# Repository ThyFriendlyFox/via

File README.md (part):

# Via

[Website](https://via-kappa-five.vercel.app) · [Contract](WORKCENTER.md) · [Status](ee-agent-kit/STATUS.md) · [Roadmap](ee-agent-kit/ROADMAP.md)

Via is the EE Workcenter. A workcenter is a set of tools, skills and gates
that an agent steps into to do one kind of work well. This one does
electronics: it turns a KiCad 10 project into fabrication outputs that
passed every gate.

<a href="https://via-kappa-five.vercel.app">
  <picture>
    <source media="(prefers-color-scheme: dark)" srcset="site/media/hero-dark.png">
    
  </picture>
</a>

The fixture board `tests/boards/pass-first-design`: lines of its design
file, then the schematic and the routed board that `workcenter design`
writes from the file. The middle card shows the circuit's part of the
sheet.

2 runs of the gates, as the terminal printed them: that board, and a
fixture board with a clearance error on purpose.

```text
$ workcenter gates tests/boards/pass-first-design
PASS   erc        0 errors, 0 warnings  [0.41s]
PASS   drc        0 errors, 0 warnings (0 unconnected, 0 parity)  [0.75s]
PASS   sim        1 decks, 46 corner runs, 0 failures  [0.23s]
PASS   export     4/4 outputs, 22 gerber files  [1.6s]
GREEN: divider  report /home/user/via/tests/boards/pass-first-design/build/gates.json

$ workcenter gates tests/boards/fail-drc-clearance
PASS   erc        0 errors, 0 warnings  [0.27s]
FAIL   drc        1 errors, 1 warnings (0 unconnected, 0 parity)  [0.63s]
       - error: clearance: Clearance violation ( clearance 0.2000 mm; actual 0.0500 mm)
       - warning: track_dangling: Track has unconnected end
RED: rc_divider  report /home/user/via/tests/boards/fail-drc-clearance/build/gates.json
```

<table>
  <tr>
    <td width="50%"></td>
    <td width="50%"></td>
  </tr>
  <tr>
    <td>The same board, turned. <code>workcenter render</code> draws it with <code>--views spin</code>.</td>
    <td>Each layer that holds something. <code>workcenter render</code> draws 1 picture for each and this sheet.</td>
  </tr>
</table>

The 3D views show the part bodies of KiCad's own library. `install.sh`
installs none of them, and without them the same command draws the bare
board. [site/media/README.md](site/media/README.md) has each picture, how
to fetch the 3 bodies, and the whole command that draws it.

## An example: Herald, a fire alarm communicator

[`examples/fire-alarm-communicator/v0.1`](examples/fire-alarm-communicator/v0.1/README.md) sits
beside a fire alarm panel and reports to a monitoring station over LTE-M, with Wi-Fi as the second
path. 84.4 x 64 mm, 4 layers, every part on the front, red with a white legend and black terminals.
It answers the panel's own phone dialer as if it were the line: a current-limited loop feed, dial
tone and the handshake from a PWM pin, and the panel's DTMF digits decoded in firmware with a
Goertzel filter. 3 supervised inputs read a closed contact, a whole loop and a cut wire apart at
every corner, and a fail-safe relay tells the panel when Herald itself fails.

## An example: Rosetta, a universal controller

[`examples/universal-controller/v0.2`](examples/universal-controller/v0.2/README.md) is a game
controller made with the workcenter: a 5-position knob picks a PS4, a PS5, an Xbox, a Switch or
Bluetooth. Its board is laid out like an Xbox 360 controller's, 148 x 82 mm, 6 layers, routed
and GREEN: thumbsticks soldered on (the footprint written from ALPS's drawing), Hall-effect
triggers on the shoulder horns, an RP2040 that runs a second USB port in software to relay a
console's signature to a licensed donor, an ESP32 whose antenna hangs past the dip between the
horns, and a knob read as 1 number whose 5 positions 6 decks prove never meet.

## An example: Signet, a mouse worn as a ring

[`examples/ring-mouse`](examples/ring-mouse/README.md) is a mouse you wear on the index finger, made
with the workcenter as a series of prototypes, a version per pass of a loop. Six 4-layer boards, 12
mm along the finger, sit on the faces of a hexagonal prism round it, each soldered to the next by 8
plated edge pads. The ring turns with the hand and the cursor follows its gyroscope; the thumb slides
along a 3-channel strip to scroll and presses the side to click. A Bluetooth LE module, a charger,
a 3.3 V rail and a 20 mAh cell ride on the other tiles, and every tile is GREEN.

## An example: Hush, a speaker that cancels noise

<table>
  <tr>
    <td width="50%"></td>
    <td width="50%"></td>
  </tr>
</table>

[`examples/anc-speaker/v0.1`](examples/anc-speaker/v0.1/README.md) is a ring 62 mm across that
sits on the face of a 40 mm speaker. A microphone on its hub listens 4 mm in front of the cone, and
an analog feedback loop plays the inverse of what it hears: 7 decks hold 3 dB less noise at 50 Hz
and 12 dB from 200 to 300 Hz at every one of 986 corner runs, and take a 150 Hz hum 18.8 dB down
(13.4 dB at the worst corner). Music from a phone plays through the loop as its target. The back
draws the idea: the noise and its inverse, meeting as one line.

## An example: Wyvern, a Snapdragon development board

[`examples/snapdragon-dev-board`](examples/snapdragon-dev-board/README.md) is a development board
with a Snapdragon on it, laid out like a Teensy and kept as version folders. v0.2 is one flat board,
76.2 x 53.34 mm, 6 layers, 2 rows of 30 pins: a Qualcomm QCS6490 on Vantron's VOSM6490 is soldered
straight on by its 662 pads, a land pattern generated from SGET's OSM standard. An RP2350 beside it
drives the pins at 3.3 V, and Linux flashes it over USB. A buck-boost holds the module's 5.0 V from
any USB-C cable, and an HD3SS3220 switches its USB 3 lane to the side the plug is on; the lane and
the converter's 0.25 mm power pads are drawn by hand in the design file.

## An example: Basalt, a microATX Threadripper board

[`examples/threadripper-matx`](examples/threadripper-matx/README.md) is a workstation motherboard
for an AMD Threadripper on sTR5, on a microATX board (244 x 244 mm), which no maker has built. It is
a prototype series built in a loop logged in its [`LOOP.md`](examples/threadripper-matx/LOOP.md),
one version a feature, each GREEN: v0.1 the floor plan, a 4844-land socket and 14 phases with every
supply in a pour; v0.2 the 4 DDR5 channels, 576 traces drawn by rule with 0 DRC errors on the first
run; v0.3 the ports and headers a desktop board carries, routed by the project's own grid router.
10 layers, black and silver.

## A chip: acc8, an 8-bit processor

Via also takes a chip from RTL to a GDSII mask layout: the drawing a
foundry etches from. The project is Verilog, benches, timing constraints
and `chip.json`. 10 gates run in order on open engines and the open
SkyWater 130 nm process, and stop at the first that does not pass.

<table>
  <tr>
    <td width="50%"></td>
    <td width="50%"></td>
  </tr>
  <tr>
    <td>The layout of <code>tests/chips/pass-acc8</code>, every layer: 760 cells on a die of 152.38 um by 152.38 um. <code>workcenter chip render</code> draws it.</td>
    <td>The second metal layer alone. The command draws 1 picture for each routing layer.</td>
  </tr>
</table>

acc8 is an accumulator processor with 16 opcodes and 4 programs in its
ROM. 5 benches make 1098 checks on the RTL, 4 of them again on the
routed netlist. The run, as the terminal printed it:

```text
$ workcenter chip gates tests/chips/pass-acc8 --strict
PASS   lint       4 RTL files, top acc8, 0 failures  [0.19s]
PASS   sim        5 benches, 1098 checks, 18 of 18 changes of the RTL caught, 0 failures  [0.74s]
PASS   synth      760 cells, 132 flops, 8530.7 um2, the mapping removed 24 flops that nothing reads (--json names each), 0 failures  [1.84s]
PASS   layout     8379.29 um2 of cells, utilisation 0.493, 0 failures  [194.64s]
PASS   sta        15 corners, least setup slack 25.1717 ns at max_ss_n40C_1v60, least hold slack 0.2974 ns at min_ff_n40C_1v95, 0 failures  [4.56s]
PASS   glsim      4 benches on the final netlist, 1 on the RTL only, 0 failures  [0.51s]
PASS   drc        2 decks: magic 0, klayout-mr 0, 0 failures  [15.16s]
PASS   antenna    the routed database, 0 failures  [0.31s]
PASS   lvs        the layout against the netlist with its supply pins: 792 devices against 792, 0 failures  [2.82s]
PASS   export     22 files, 20 reports and manifest.json in chip/tapeout, 0 failures  [0.37s]
scope: open engines, sky130A 1.0.470-0-g6d4d117, decks: magic (community), klayout-mr (community), corners: max_ss_n40C_1v60, max_ss_100C_1v60, max_ff_n40C_1v95, max_ff_100C_1v95, max_tt_025C_1v80, min_ss_n40C_1v60, min_ss_100C_1v60, min_ff_n40C_1v95, min_ff_100C_1v95, min_tt_025C_1v80, nom_ss_n40C_1v60, nom_ss_100C_1v60, nom_ff_n40C_1v95, nom_ff_100C_1v95, nom_tt_025C_1v80; no foundry deck ran; no shuttle's limits were checked
GREEN: pass-acc8  report /home/user/via/tests/chips/pass-acc8/build/gates.json
```

| Gate | What it holds |
|---|---|
| LINT, SIM | The RTL reads the same to a simulator and to a synthesizer. Every bench passes, and every listed change of the RTL fails a bench: a bench that passes on a wrong design proves nothing. |
| SYNTH, LAYOUT | The RTL maps onto the library's cells, with a reset on every flop. The cells are placed and routed with no violation. |
| STA, GLSIM | Timing holds at every corner of temperature and supply the project names, with the routed wires. The benches pass again on the routed netlist. |
| DRC, ANTENNA, LVS | The layout breaks no rule of 2 decks, no wire collects too much charge, and the layout is the netlist, device by device. |
| EXPORT | The layout is handed out only when each of the 9 gates passed on the files as they are now. |

The line before the verdict is the scope of the run. GREEN says that the
open engines found no fault in these files. It does not say that a foundry
accepts the layout or that the silicon works: no foundry deck runs here.

The engines install on request: `sudo ./install.sh --chip`.
`workcenter chip init <dir> --top <module>` starts a project, and
`workcenter next <dir>` names each step from there.
[`.claude/skills/chip-design/SKILL.md`](.claude/skills/chip-design/SKILL.md)
has the procedure, and [`tests/chips/README.md`](tests/chips/README.md)
the 9 fixture chips.

## What it does

| Part | In short |
|---|---|
| **Engines** | KiCad 10 (`kicad-cli`), ngspice, FreeRouting. |
| **Gates** | ERC, DRC, SIM, EXPORT, in that order. A board is done when `workcenter gates <project>` prints GREEN. |
| **Design as code** | `workcenter design design.py --route` builds a schematic and a routed board from a Python file that names parts from the KiCad libraries. No GUI at any step. |
| **A schematic that simulates** | The design file says how each part simulates (`d.sim`, `d.no_sim`), and the schematic KiCad opens exports a netlist ngspice runs. A pin map KiCad would complete by position is refused first. |
| **Decks** | The SIM gate runs the decks under `sim/` and holds each measured value to its bound. A deck is a file of its own. Nothing holds a deck typed by hand to the schematic's parts yet: the roadmap names that gap. |
| **Corners** | The SIM gate runs every deck at each temperature the project names and with each part at each end of its tolerance. It runs every combination of those ends up to 64 runs, and a worst case for each bound above that. It also runs the Monte Carlo draws the project names. A bound holds at every corner or it does not hold. |
| **Frequency plan** | The SIM gate holds every switching frequency and its harmonics against every resonance a deck measured. |
| **The next step** | `workcenter next <project>` names the one step that is left, its command, and the fix for the first failure. A person or an agent of any size follows the same path. |
| **Skills** | Procedures for each kind of step, as Markdown files. |
| **Fixture boards** | The tests. Each passes everything or fails 1 named gate. |

## How it works

<picture>
  <source media="(prefers-color-scheme: dark)" srcset="site/media/diagram-dark.png">
  
</picture>

A design file becomes a KiCad project. The 4 gates judge the project in
order and stop at the first red. The last line of a run is the verdict:
GREEN, RED or SKIPPED. The fabrication outputs of a GREEN board are in
`build/fab/`.

## Quick start

```sh
sudo ./install.sh     # Ubuntu 24.04: KiCad 10, ngspice, Java 21, FreeRouting
workcenter doctor     # each engine's status; ok when nothing is absent
workcenter gates tests/boards/pass-first-design     # GREEN
workcenter gates tests/boards/fail-drc-clearance    # red at DRC, on purpose
workcenter next tests/boards/fail-drc-clearance     # the one next step: the fix
workcenter sim tests/boards/fail-sim-corner         # red at its corners, on purpose
workcenter sim tests/boards/fail-freq-overlap       # red on the frequency plan
```

Output goes to `<project>/build/`: `erc.json`, `drc.json`, `sim/`,
`fab/` (gerbers, drill, BOM, schematic PDF), `gates.json`.

A first board starts from a copy of the template's design file, in a
folder of its own outside this checkout:

```sh
mkdir ~/divider
cp templates/project/design.py ~/divider/
workcenter design ~/divider/design.py --route    # the KiCad project, routed
workcenter gates ~/divider --strict              # GREEN, and SIM has no deck to run yet
```

[`.claude/skills/board-design/SKILL.md`](.claude/skills/board-design/SKILL.md)
has the procedure from a spec to a GREEN board.

## Commands

`workcenter --help` describes each command, and
`workcenter <command> --help` lists its flags.
[`ee-agent-kit/docs/CONFIGURATION.md`](ee-agent-kit/docs/CONFIGURATION.md)
has every flag.

<details>
<summary>The 25 commands</summary>

| Command | What |
|---|---|
| `doctor` | Report each engine's status. |
| `next` | Name the one next step for a project. |
| `chip` | A chip project, from RTL to a GDSII layout: `chip init`, `chip gates`, 1 command for each of its 10 gates, and `chip render` for a picture of the layout. Tests hold all 10 gates. The acceptance design, an 8-bit processor of 760 cells on the sky130A process, is GREEN with `--strict` in under 4 minutes. |
| `design` | Build a design file into a KiCad project; `--route` routes it; `--check` compares. |
| `erc`, `drc`, `sim`, `export` | One gate, alone. |
| `gates` | The 4 gates in order; the last line is the verdict. |
| `verify` | Check a verification package against a fresh run; say whether the requirements are met. |
| `autoroute` | Write FreeRouting's session file for a hand-drawn board's DSN. The import into KiCad is by hand. |
| `inspect` | Read a routed board: `map`, `list`, `probe`, `net`, `islands`, `resistance`, `crossed`. |
| `placement` | Run a kistack placement check on a board. |
| `render`, `pictures` | Images of the schematic, the board, every layer; turning GIFs; assembly scenes. |
| `procure`, `costs` | Price a board's parts; price every board of every version. |
| `sources`, `fetch`, `curve` | Check each part's datasheet and model; fetch one; read a curve from a PDF. |
| `mutate` | Prove a firmware's host tests can fail. |
| `ci` | Replay a repository's GitHub workflow here. |
| `docs`, `version`, `diagram` | A version's contents page and datasheets; a new version folder; a block diagram. |

</details>

## Where it runs

**A Claude Code cloud environment.** The environment carries the
software; the project's repository carries the board. Create an environment
whose setup script is the 3 lines in
[`environment/setup.sh`](environment/setup.sh), with the network hosts from
[`environment/README.md`](environment/README.md). Open any project's
repository in it. Attach this repository as a second repository when its
skills should load.

**Another agent host.** `AGENTS.md` at the root is the entry for a host
that does not read `CLAUDE.md`; the 2 files are the same text. Every
procedure is a Markdown file under `.claude/skills/`, and every check is a
command. `workcenter next <project>` gives the step, and `make verify`
the repository's health.

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
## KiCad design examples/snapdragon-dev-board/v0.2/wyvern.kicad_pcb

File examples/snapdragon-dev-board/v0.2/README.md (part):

# Wyvern — board prototype v0.2

> The current version of the [Wyvern prototype series](../README.md), started as a copy of [`../v0.1/`](../v0.1/). The earlier version is the sibling folder [`../v0.1/`](../v0.1/).

A development board with a Snapdragon on it, on one flat board. The Qualcomm QCS6490 (8 Kryo 670
cores, 1 at 2.7 GHz, 3 at 2.4 GHz and 4 at 1.9 GHz; an Adreno 643; a Hexagon NPU of 12 TOPS; 8 GB of
LPDDR5 and 64 GB of eMMC) comes on Vantron's VOSM6490, a 45 x 45 mm OSM Size-L module that is soldered
straight onto the board by its 662 pads, like any other chip, and runs Linux or Android. Beside it, an
RP2350 drives 30 pins at 3.3 V the way a Teensy's microcontroller does; the Snapdragon resets it,
puts it in its bootloader and talks to it over USB, so Linux flashes it. The Snapdragon's own UART,
2 I2C buses, an SPI bus and 2 GPIOs are on the same rows at the module's end, at 1.8 V. One USB-C
cable powers the board and carries USB 3.

Wyvern lies flat on a bench, or stands in a breadboard on its 2 rows of pins, with one USB-C cable
at its left end. It is one board, 76.2 x 53.34 mm (3.0 x 2.1 inch) and 6 layers, with the module,
the USB-C, the power and the RP2350 on its top face and the microSD slot and the pins' names on its
bottom.

This folder is a whole KiCad 10 project made with the EE Workcenter: `design.py` is the board, and
the `.kicad_*` files beside it are what `workcenter design` writes from it.

| Item | State |
|---|---|
| Schematic | drawn with wires in blocks, the module's 662 pins in 13 banks named from the OSM standard and Vantron's datasheet; ERC <!-- erc -->0 errors, 0 warnings<!-- /erc -->; no parity warning |
| Board | 76.2 x 53.34 mm (3.0 x 2.1 in), **6 layers**, 1.6 mm, black mask, white legend, ENIG, made to Sierra Circuits' Web PCB limits; 2 rows of 30 pins on the 0.1 in grid, 2.0 in apart; the module, USB-C, the power, the RP2350 and the buttons on the top face, the microSD and the pins' names on the bottom |
| Gates | <!-- gates -->GREEN with 16 warnings: ERC 0 and 0; DRC 0 errors, 0 unconnected, 0 parity, 9 warnings (silkscreen at the edge, 4 vias with nothing past them); SIM 7 decks, 397 corner runs, 0 failures; EXPORT 4 of 4 (`docs/gates.md`)<!-- /gates --> |
| USB | the module's SuperSpeed lane through an HD3SS3220 to both sides of the USB-C receptacle, drawn by hand as 90 ohm pairs; CC by the HD3SS3220, which answers a charger with nothing else powered; the USB 2 pair to both rows |
| Power | 5 V from USB-C (or the 5V pin) to the module's 5.0 V by a TPS552892 buck-boost, 4.86 to 5.17 V at every corner; 3.3 V from that by an AP2112K; the module's own 1.8 V on 2 pins |
| Simulation | 7 decks, each at every corner of its parts' tolerances (`sim/`): the 5.0 V rail inside the module's window, where the converter starts, the USB input's resonance with a cable, the Snapdragon's I2C on the pins, the RP2350's reset and boot lines; a frequency plan holds the 3 clocks against the resonance |
| Parts and cost | an orderable part for every line (`../parts/catalog.csv`); the board's parts $34.18 for 1, $26.00 each for 10, with 4 lines not priced and each reason named; 7 lines out of stock at Digi-Key when read, most with a restock date; the module is sold by quote and not priced |
| Firmware | none yet |

## Images

| Top face | Bottom face (mirrored) |
|---|---|
|  |  |

| 3D, from above | 3D, from below |
|---|---|
|  |  |

| Turning, from above | Turning, from below |
|---|---|
|  |  |

| Every layer | The schematic |
|---|---|
|  |  |

From `workcenter pictures .` (its `pictures.json`), with KiCad's 3D bodies in `KICAD10_3DMODEL_DIR`
and the 5 bodies in `models/`. The module's body is a stand-in ("The Snapdragon module").

## What changed in v0.2: one flat board

The request, on 2026-11-12: "there's a LOT of open hinges here, power, data, alot of routing, it
looks like you slapped two board together too. Can it be one board for v0.2?"

| Finding | The owner's answer | What v0.2 does |
|---|---|---|
| v0.1 is 2 boards: the Open-Q 845 module stands 3 mm over the carrier on 3 sockets, 300 contacts to buy, align and mate | chose "Flat QCS6490 module" (2026-11-12): one flat board, about 53 x 76 mm, a 45 mm QCS6490 module soldered straight on, no sockets and no second board; 5 V in, 3.3 V pins along both long edges, USB-C at one end | the VOSM6490 sits on its 662-pad LGA, reflowed with every other part; the board is 76.2 x 53.34 mm ("The Snapdragon module") |
| Power: v0.1's module wanted 3.45 to 4.75 V from USB's 5 V through a buck whose input stood 0.13 ohm from oscillating with a long cable; this module wants 4.8 to 5.2 V, which a cable carrying 3 A does not deliver | part of the same answer: 5 V in | a TPS552892 buck-boost makes 5.0 V from any VBUS between 3.8 and 5.5 V (4.86 to 5.17 V at every corner), and a damper holds the cable's resonance at 0.51 ohm at worst against the converter's 1.33 ohm ("Power") |
| Data: v0.1 relied on the module's own Type-C controller and lane order, which its maker documents only in a carrier guide behind a registration | part of the same answer | an HD3SS3220 owns the plug: CC, orientation and the SuperSpeed lane, and it answers a charger before anything is powered; every module pad the board uses is named from Vantron's public pin tables ("USB-C") |
| Supply: Digi-Key lists the Open-Q 845 uSOM as obsolete | part of the same answer | the VOSM6490 carries the QCS6490 on SGET's open OSM standard, so its land pattern is public and other makers' OSM-L modules share it |

### Board

The module sets the board: 45 mm square between 2 rows of 30 pins 2.0 inch apart, its row A (its
USB-C lane) facing the USB-C end, its right edge 1.0 mm from the board's. The 31 mm left of it holds
everything else on the top face: the buttons down the left edge, the RP2350 block in the upper half
(v0.1's, turned a quarter turn), USB-C, its mux and the buck-boost in the lower half. The microSD
slot sits under the far end, its card standing out past the right edge. Every module pad the board
uses has a via in the middle of the 4 pads round it (`module_fanout`), so the router takes each
signal out from under the module on the inner layers. The router (FreeRouting) drew <!-- route -->1007 segments and 76 vias round
what `design.py` draws by hand: the buck-boost's power pads, the SuperSpeed lane through its mux,
the receptacle's B row, the RP2350's supplies and fan-out, the module's 184 vias and a spine that
holds the 5 V plane together under the module<!-- /route -->.

### Simulation

7 decks, run at every corner (`workcenter sim .`): the module's 5.0 V at 4.86 to 5.17 V against
its 4.8 to 5.2 V; where the buck-boost starts, 3.51 to 3.78 V of VBUS; the USB input's peak
impedance with a cable, 0.26 ohm at 37 kHz and 0.51 ohm at the worst corner against 1.33 ohm; the
Snapdragon's I2C on the pins, the RP2350's reset and boot lines. A frequency plan holds the
buck-boost, the RP2350's regulator and its crystal against the cable's resonance.

### Firmware

None yet ("Open items").

### Parts and cost

The module, the mux, the buck-boost and its inductor, 9 resistors and capacitors and the 1 x 30
headers are new; the RP2350 block's parts are v0.1's. `../parts/catalog.csv` names an orderable part
for each line, read on 2026-11-12; `workcenter costs ..` prices the board into `../parts/lists/`
("Bill of materials").

### Verification summary

No verification package yet ("Open items").

## What changed in v0.1: the first board

The request: a new microcontroller development board, something like a Teensy but with a Snapdragon
chip, compact, as the workcenter's example of what it can make. v0.1 carried a Snapdragon 845 on
Lantronix's Open-Q 845 uSOM, plugged into 3 DF40 sockets on a 61 x 30.5 mm stick, with an RP2350 on
the pins; its folder, [`../v0.1/`](../v0.1/), tells the rest.

## Architecture

```
USB-C (J1) ─VBUS─┬─ 5V pin
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
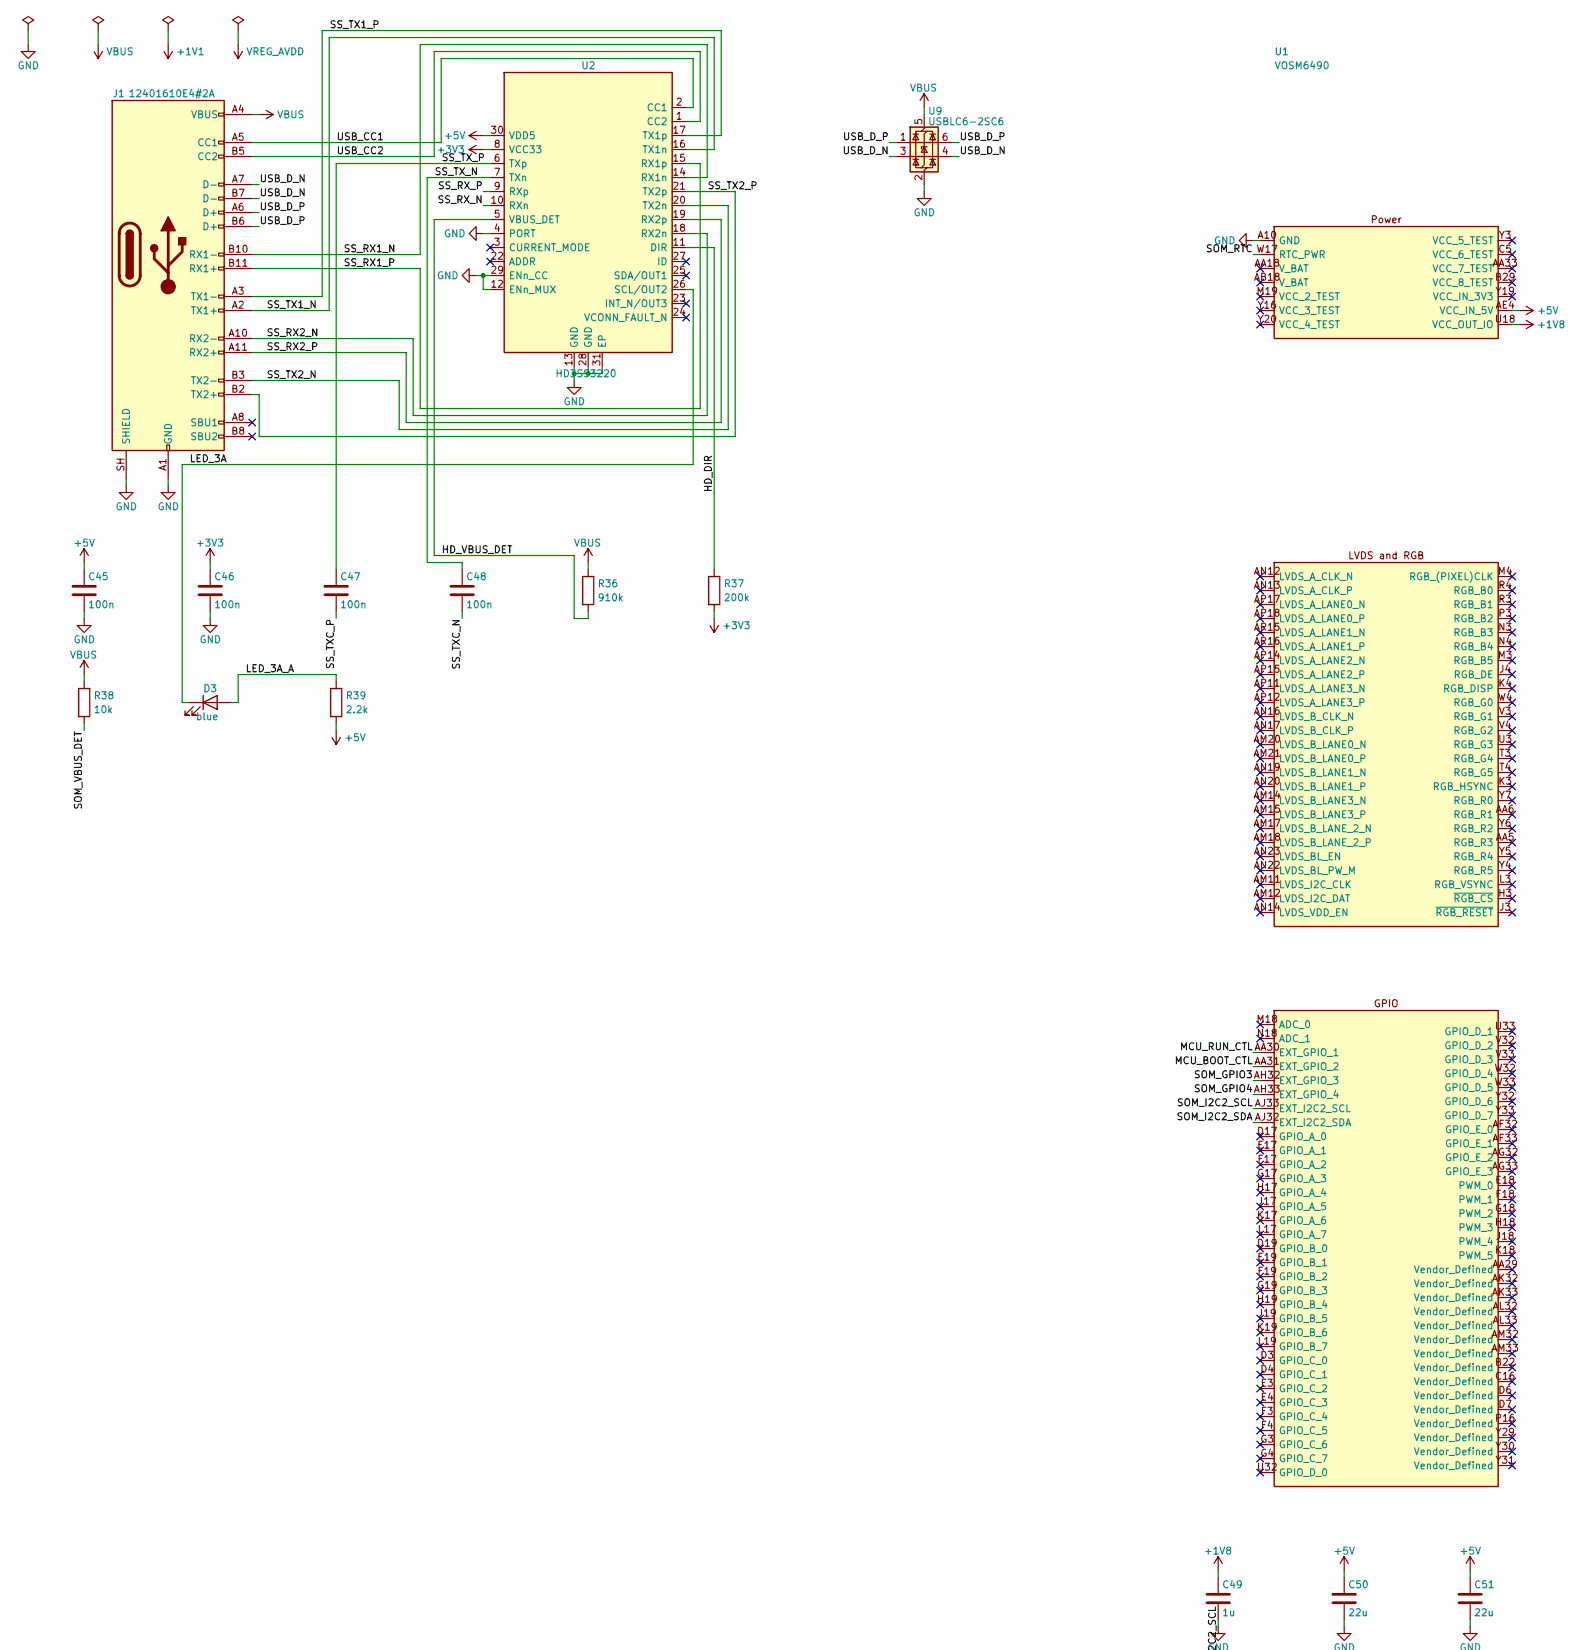
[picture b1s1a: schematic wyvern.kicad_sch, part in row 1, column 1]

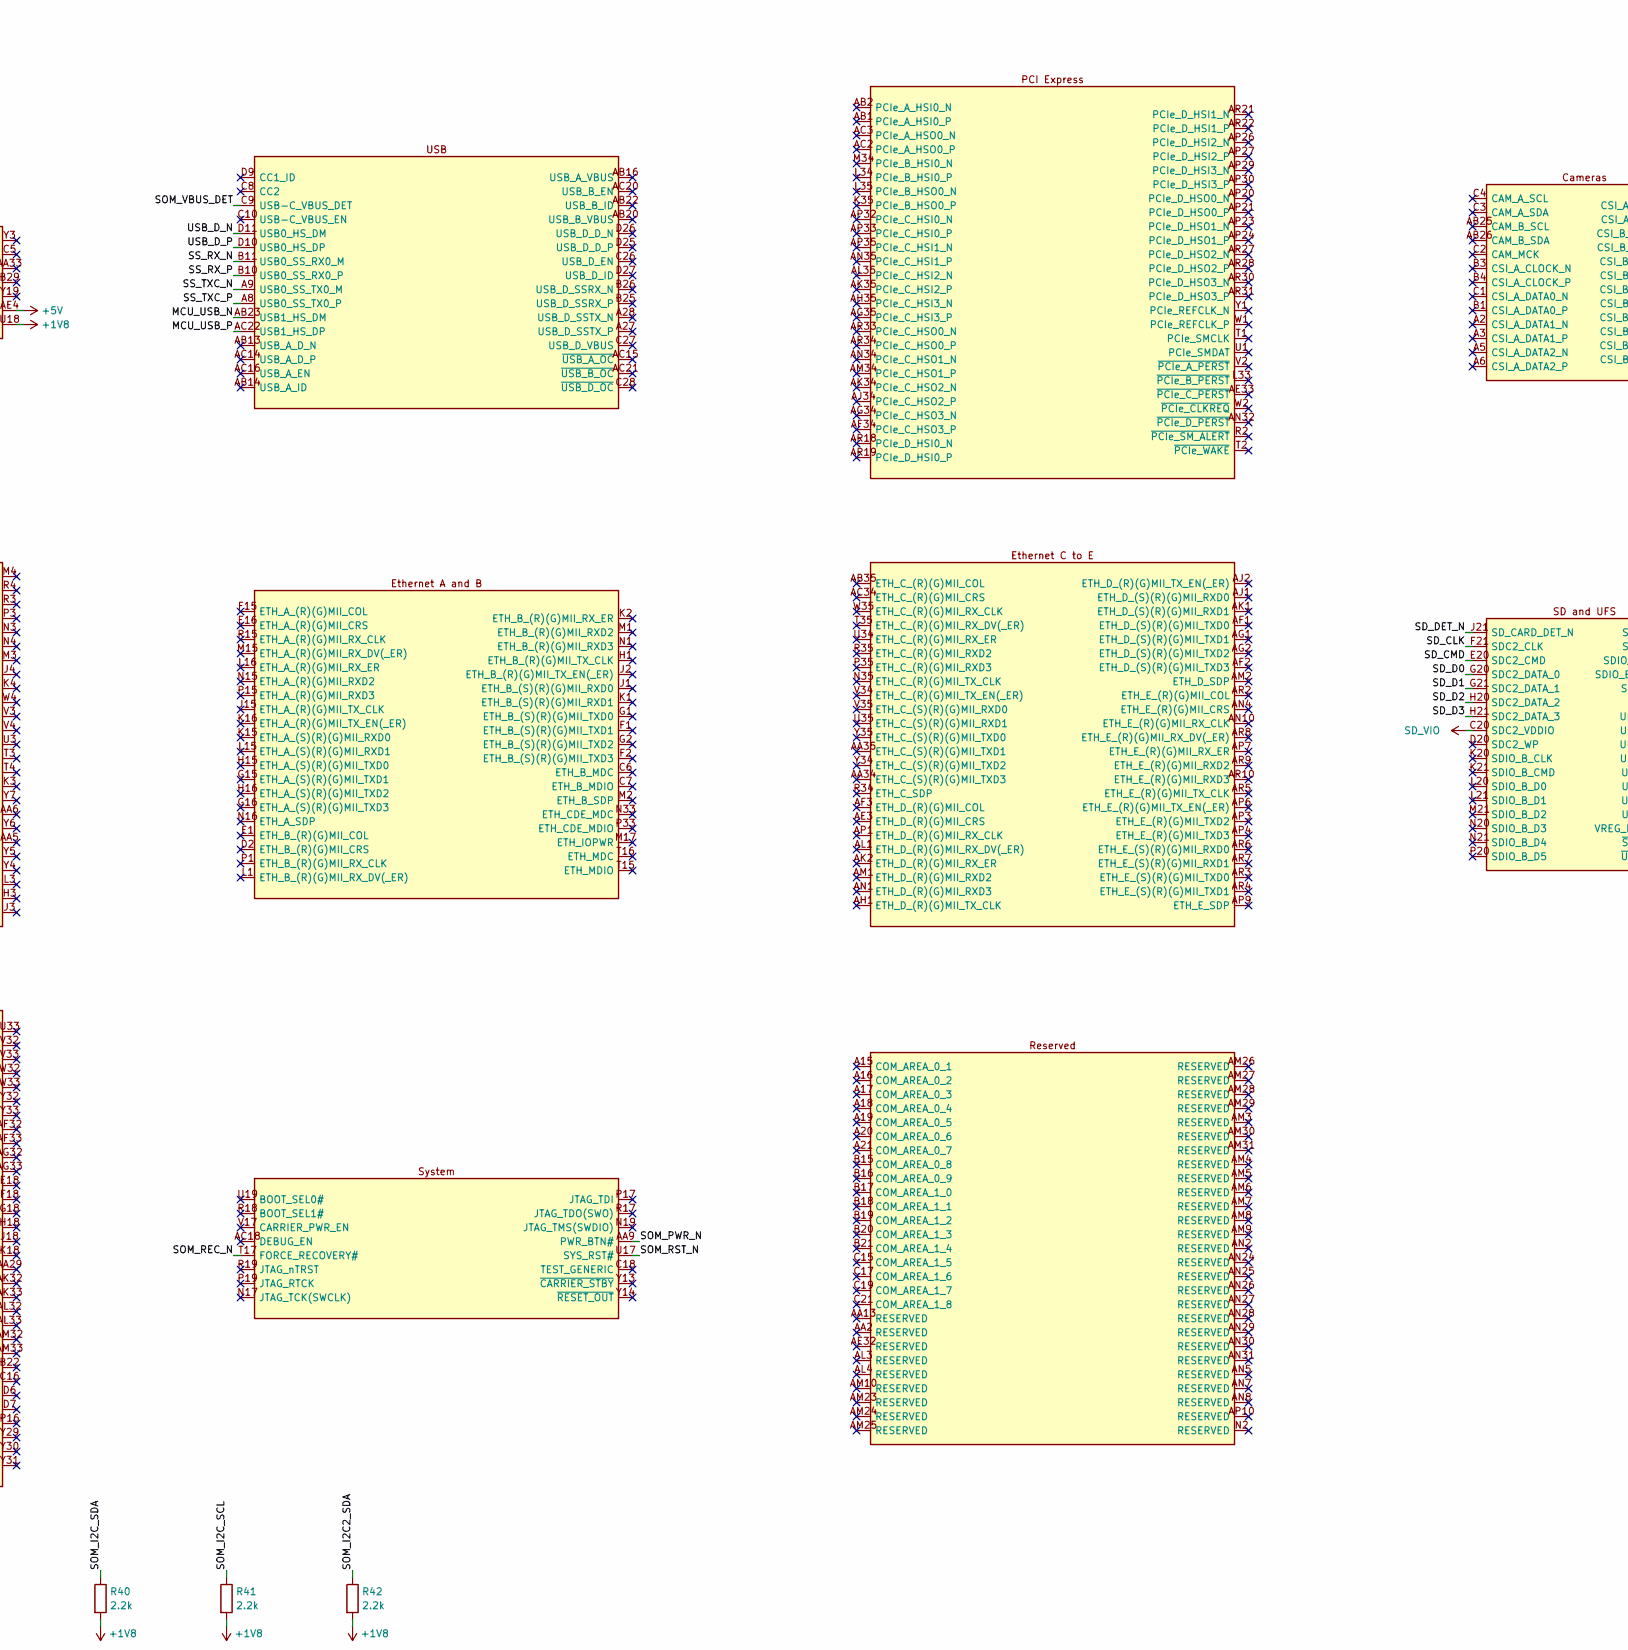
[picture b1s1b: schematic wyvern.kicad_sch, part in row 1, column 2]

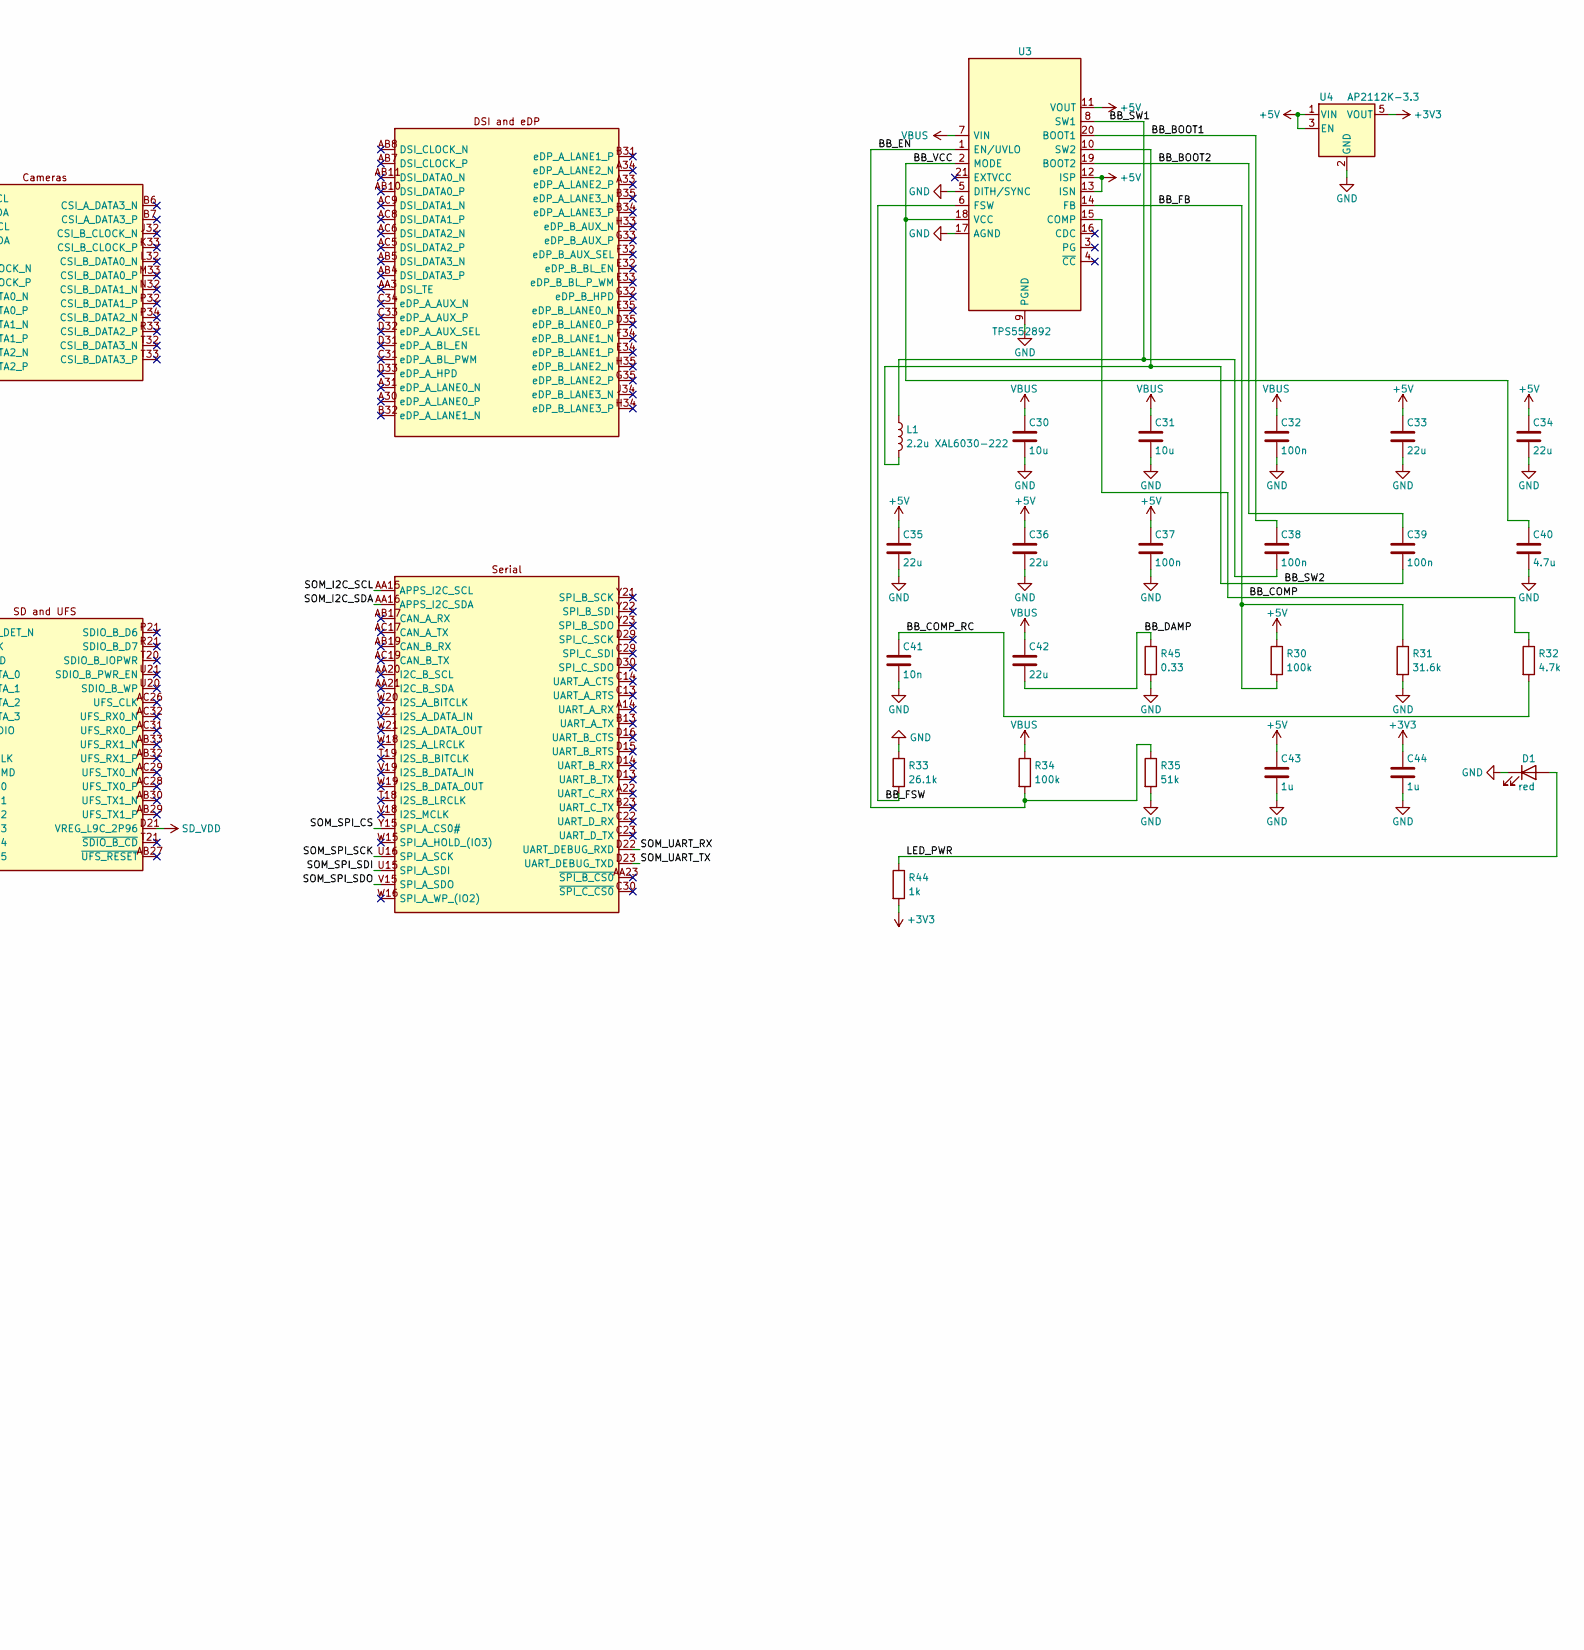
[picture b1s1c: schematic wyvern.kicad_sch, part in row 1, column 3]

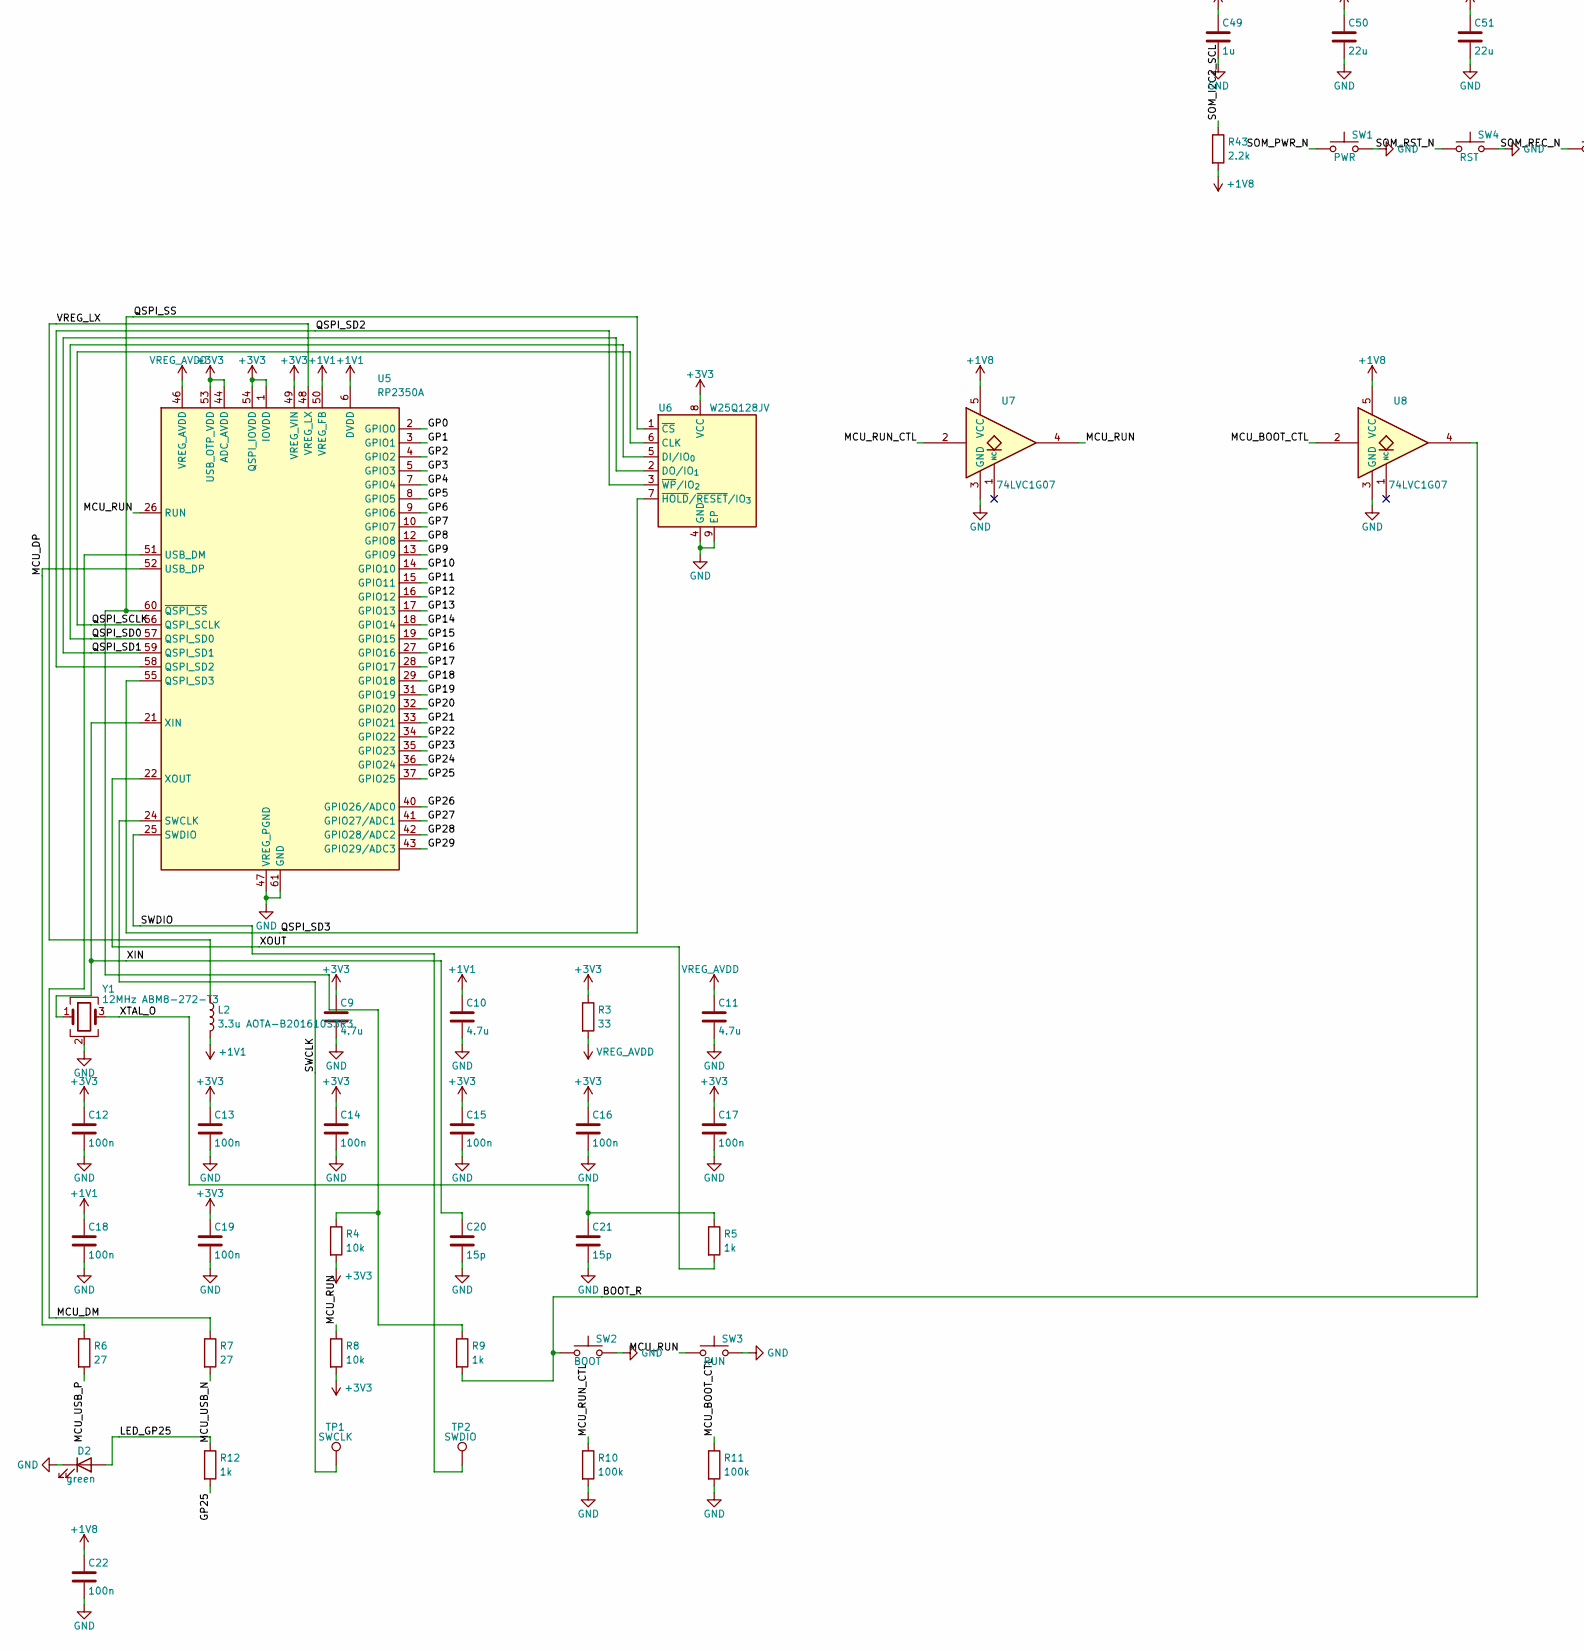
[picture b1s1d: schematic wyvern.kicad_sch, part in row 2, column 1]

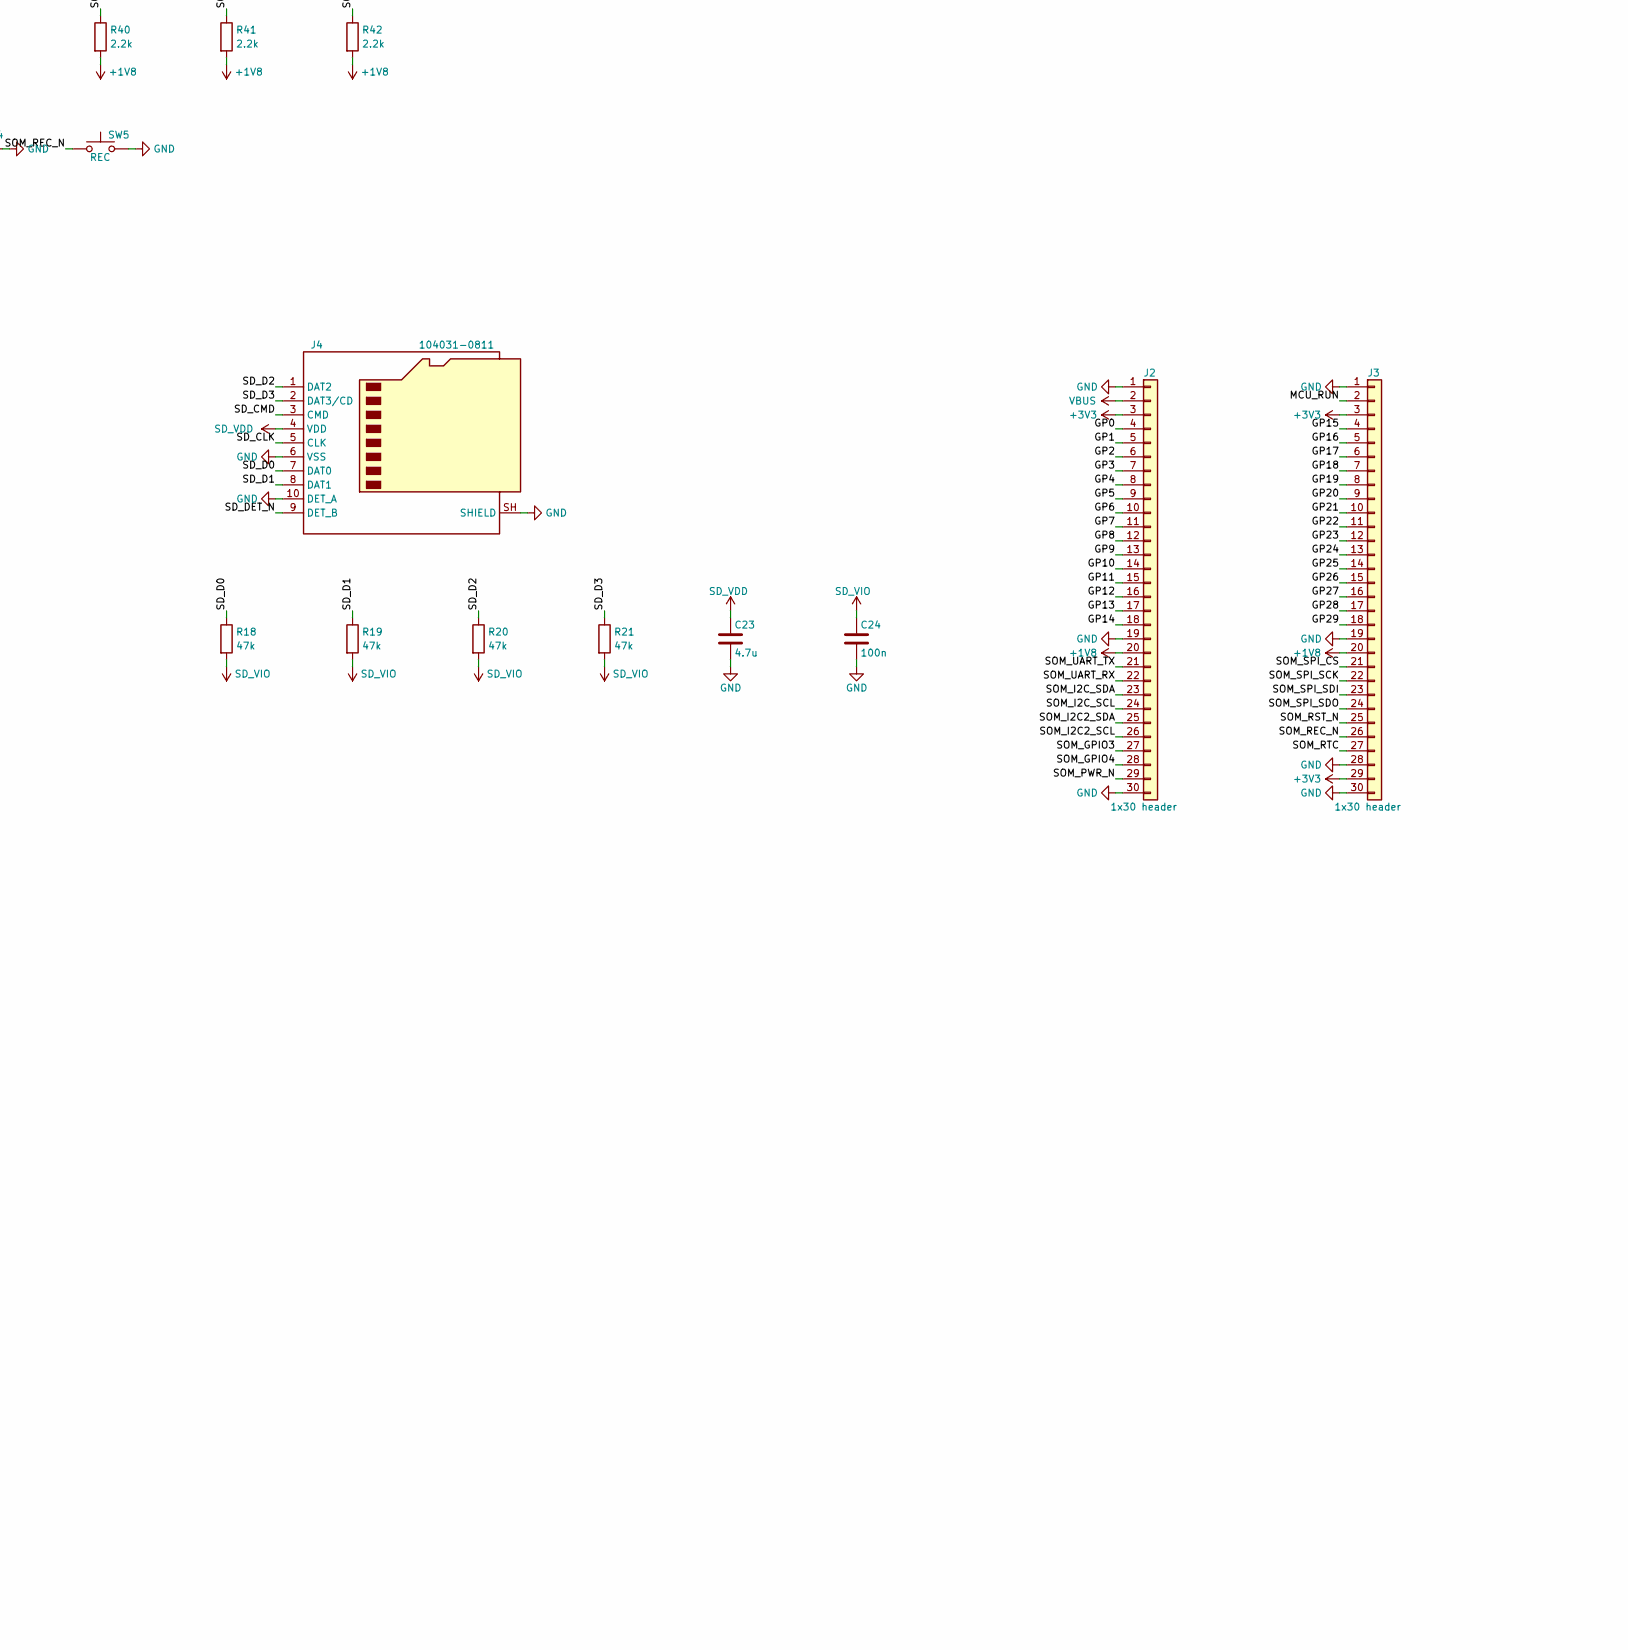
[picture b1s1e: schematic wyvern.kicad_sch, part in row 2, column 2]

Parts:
C9, C10, C11, C40: 4.7u; C_0402_1005Metric
C12, C13, C14, C15, C16, C17, C18, C19, C22, C24, C32, C37, C38, C39, C45, C46, C47, C48: 100n; C_0402_1005Metric
C20, C21: 15p; C_0402_1005Metric
C23: 4.7u; C_0603_1608Metric
C30, C31: 10u; C_0805_2012Metric
C33, C34, C35, C36, C42, C50, C51: 22u; C_0805_2012Metric
C41: 10n; C_0402_1005Metric
C43, C44, C49: 1u; C_0402_1005Metric
D1: red; LED_0603_1608Metric
D2: green; LED_0603_1608Metric
D3: blue; LED_0603_1608Metric
J1: 12401610E4#2A; USB_C_Receptacle_Amphenol_12401610E4-2A_Ring6mil
J2, J3: 1x30 header; PinHeader_1x30_P2.54mm_Vertical
J4: 104031-0811; microSD_HC_Molex_104031-0811
L1: 2.2u XAL6030-222; L_Coilcraft_XAL6030-XXX
L2: 3.3u AOTA-B201610S3R3; L_Abracon_AOTA-B201610S
R3: 33; R_0402_1005Metric
R4, R8, R38: 10k; R_0402_1005Metric
R5, R9, R12, R44: 1k; R_0402_1005Metric
R6, R7: 27; R_0402_1005Metric
R10, R11, R30, R34: 100k; R_0402_1005Metric
R18, R19, R20, R21: 47k; R_0402_1005Metric
R31: 31.6k; R_0402_1005Metric
R32: 4.7k; R_0402_1005Metric
R33: 26.1k; R_0402_1005Metric
R35: 51k; R_0402_1005Metric
R36: 910k; R_0402_1005Metric
R37: 200k; R_0402_1005Metric
R39, R40, R41, R42, R43: 2.2k; R_0402_1005Metric
R45: 0.33; R_0402_1005Metric
SW1: PWR; SW_Push_1P1T_NO_CK_KMR2
SW2: BOOT; SW_Push_1P1T_NO_CK_KMR2
SW3: RUN; SW_Push_1P1T_NO_CK_KMR2
SW4: RST; SW_Push_1P1T_NO_CK_KMR2
SW5: REC; SW_Push_1P1T_NO_CK_KMR2
TP1: SWCLK; TestPoint_Pad_D1.0mm
TP2: SWDIO; TestPoint_Pad_D1.0mm
U1: VOSM6490; OSM_L_LGA-662_45x45mm_P1.25mm
U2: HD3SS3220; Texas_RNH0030A_WQFN-30-1EP_2.5x4.5mm_P0.4mm_EP1.2x3.2mm
U3: TPS552892; Texas_RYQ0021A_VQFN-HR-21_5x3mm_P0.5mm
U4: AP2112K-3.3; SOT-23-5
U5: RP2350A; QFN-60-1EP_7x7mm_P0.4mm_EP3.4x3.4mm
U6: W25Q128JV; WSON-8-1EP_6x5mm_P1.27mm_EP3.4x4.3mm
U7, U8: 74LVC1G07; SOT-353_SC-70-5
U9: USBLC6-2SC6; SOT-23-6
Y1: 12MHz ABM8-272-T3; Crystal_SMD_3225-4Pin_3.2x2.5mm

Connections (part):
+1V1: C10.1, C18.1, L2.2, U5.6 (DVDD), U5.23 (DVDD), U5.39 (DVDD), U5.50 (VREG_FB)
+1V8: C22.1, C49.1, J2.20, J3.20, R40.2, R41.2, R42.2, R43.2, U1.U18 (VCC_OUT_IO), U7.5 (VCC), U8.5 (VCC)
+3V3: C9.1, C12.1, C13.1, C14.1, C15.1, C16.1, C17.1, C19.1, C44.1, C46.1, J2.3, J3.3, J3.29, R3.1, R4.2, R8.2, R37.2, R44.2, U2.8 (VCC33), U4.5 (VOUT), U5.1 (IOVDD), U5.11 (IOVDD), U5.20 (IOVDD), U5.30 (IOVDD), U5.38 (IOVDD), U5.44 (ADC_AVDD), U5.45 (IOVDD), U5.49 (VREG_VIN), U5.53 (USB_OTP_VDD), U5.54 (QSPI_IOVDD), U6.8 (VCC)
+5V: C33.1, C34.1, C35.1, C36.1, C37.1, C43.1, C45.1, C50.1, C51.1, R30.1, R39.2, U1.AE4 (VCC_IN_5V), U1.AF4 (VCC_IN_5V), U1.AG4 (VCC_IN_5V), U1.AH3 (VCC_IN_5V), U1.AH4 (VCC_IN_5V), U1.AJ3 (VCC_IN_5V), U1.AJ4 (VCC_IN_5V), U1.AK4 (VCC_IN_5V), U1.Y8 (VCC_IN_5V), U1.Y9 (VCC_IN_5V), U1.Y10 (VCC_IN_5V), U1.Y11 (VCC_IN_5V), U1.Y17 (VCC_IN_5V), U1.Y25 (VCC_IN_5V), U1.Y26 (VCC_IN_5V), U1.Y27 (VCC_IN_5V), U1.Y28 (VCC_IN_5V), U2.30 (VDD5), U3.11 (VOUT), U3.12 (ISP), U3.13 (ISN), U4.1 (VIN), U4.3 (EN)
/BB_BOOT1: C38.1, U3.20 (BOOT1)
/BB_BOOT2: C39.1, U3.19 (BOOT2)
/BB_COMP: R32.1, U3.15 (COMP)
/BB_COMP_RC: C41.1, R32.2
/BB_DAMP: C42.2, R45.1
/BB_EN: R34.2, R35.1, U3.1 (EN/UVLO)
/BB_FB: R30.2, R31.1, U3.14 (FB)
/BB_FSW: R33.2, U3.6 (FSW)
/BB_SW1: C38.2, L1.1, U3.8 (SW1)
/BB_SW2: C39.2, L1.2, U3.10 (SW2)
/BB_VCC: C40.1, U3.2 (MODE), U3.18 (VCC)
/BOOT_R: R9.2, SW2.1, U8.4
/GP0: J2.4, U5.2 (GPIO0)
/GP1: J2.5, U5.3 (GPIO1)
/GP2: J2.6, U5.4 (GPIO2)
/GP3: J2.7, U5.5 (GPIO3)
/GP4: J2.8, U5.7 (GPIO4)
/GP5: J2.9, U5.8 (GPIO5)
/GP6: J2.10, U5.9 (GPIO6)
/GP7: J2.11, U5.10 (GPIO7)
/GP8: J2.12, U5.12 (GPIO8)
/GP9: J2.13, U5.13 (GPIO9)
/GP10: J2.14, U5.14 (GPIO10)
/GP11: J2.15, U5.15 (GPIO11)
/GP12: J2.16, U5.16 (GPIO12)
/GP13: J2.17, U5.17 (GPIO13)
/GP14: J2.18, U5.18 (GPIO14)
/GP15: J3.4, U5.19 (GPIO15)
/GP16: J3.5, U5.27 (GPIO16)
/GP17: J3.6, U5.28 (GPIO17)
/GP18: J3.7, U5.29 (GPIO18)
/GP19: J3.8, U5.31 (GPIO19)
/GP20: J3.9, U5.32 (GPIO20)
/GP21: J3.10, U5.33 (GPIO21)
/GP22: J3.11, U5.34 (GPIO22)
/GP23: J3.12, U5.35 (GPIO23)
/GP24: J3.13, U5.36 (GPIO24)
/GP25: J3.14, R12.2, U5.37 (GPIO25)
/GP26: J3.15, U5.40 (GPIO26/ADC0)
/GP27: J3.16, U5.41 (GPIO27/ADC1)
/GP28: J3.17, U5.42 (GPIO28/ADC2)
/GP29: J3.18, U5.43 (GPIO29/ADC3)
/HD_DIR: R37.1, U2.11 (DIR)
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

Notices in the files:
README.md:
License:
MIT; see [LICENSE](LICENSE). KiCad, ngspice, and FreeRouting keep their
own licenses. Inter, the website's font, is under the SIL Open Font
License: [site/fonts/LICENSE](site/fonts/LICENSE).
License: MIT
